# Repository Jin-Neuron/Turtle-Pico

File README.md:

<div align="right">
  <a href="README_en.md">English</a> | <b>日本語</b>
</div>

# Turtle Pico - 配線いらずで、本格的な電子工作を -

こんにちは！皆さんは、**電子工作でのお困りごと**を、どのように解決しますか？

煩雑な配線、難しいプログラミングと困難な環境構築、毎回確認が面倒なピン配置...などなど、電子工作を楽しんでいると、いくつもの壁に突き当たります。

そんな課題を克服できるようにと開発したのが、このTurtle Pico マイコンボード。ブレッドボードすら不要で、**コネクタに直接部品を接続するだけ**で回路が完成します。内部には**Raspberry Pi Pico W**を搭載しているので、プログラミングには**MicroPython**を使用でき、更にリソースにも困りません！

コネクタに超音波センサを指すと、その容姿はまるで亀のようで、その容姿から「**Turtle Pico**」とボードを名付けました。

ボードの詳細仕様は、 [Turtle Pico 仕様書](https://jinproduction.work/wp-content/uploads/2024/07/specific_ja.pdf)をご覧ください！

**本PJは現在、製品化に向けて準備中です。**

## Turtle Pico 製品パッケージ

Turtle Picoは、画像のような**パッケージ**に収納されています。

中を開けるとこのようになっていて、本体と外箱の寸法は画像に記載のとおりです。黄色が外箱、ピンクが本体の寸法です。

パッケージの中に、更にTurtle Pico本体がありますが、本体は基板を**オリジナル3Dプリンタ製カバー**で覆うような形状をしています。USBやMicroSDカードなどのコネクタポートがロゴで表示されています。

それぞれの意味は、[Turtle Pico 仕様書](https://jinproduction.work/wp-content/uploads/2024/07/specific_ja.pdf) にてご確認ください。

Turtle Picoは本体カバーの色で**カラーバリエーション**が4色あり、**ピンク色、緑色、グレー、空色**となっています。

## Turtle Pico ワクワク作例ブック

製品化モデルでは、上記の作例集が付属します。ソースコードを [example](./example/)に掲載している、TurtlePico作例の数々の作り方を掲載しています。

ここでは、作例集に掲載している、いくつかの**Turtle Picoの仲間たち**をご紹介しましょう。

画像左上は4脚でよちよちと歩くロボット「**Turtle Pico Robot**」で、サーボモータの回転で歩きます。その右側にあるのはドローン「**Turtle Pico Drone**」、更にその下にはマイコンカー「**Turtle Pico Car**」があります。

これらは、上に乗せるものを変えたり、様々な制御を追加することで、**いろいろな応用**が効きそうです。ぜひ、作例集を参考に、**自分専用のアプリケーション**に仕上げてください！

画像左下には、Turtle Picoを**サウンドカード**にしてスピーカーで音楽を流している作例です。Turtle Picoに搭載されているPCM5102AというオーディオDACは、**32bit / 192kHz**にも対応しているため、ハイレゾ音源も流せるパワフルなオーディオDACとなります。

従って、TurtlePicoは、公式にある**サウンドカード**のファームウェアを使用すれば、周囲にアンプやスピーカーをつないで、**クラフトオーディオ**を楽しむことができるボードにもなります。

作例集では、これら作例の作り方を始めとし、**応用の仕方を設計からデバッグまで**、最近の「**バイブコーディング**」でかんたんに行う**製作方法**を解説しています。Turtle Picoをお買い上げいただければ、セット担っているので、ぜひお買い求めください！

<!-- 

## Case

Turtle Pico Package is available in [**board/main/Case**](https://github.com/Jin-Neuron/Turtle-Pico/tree/master/board/main/Case).

## Purchase your board

Turtle Pico boards can currently only be purchased from [PCBWay's Shared Project Page](https://www.pcbway.com/project/shareproject/Turtle_Pico_Board_c183b11f.html). Once officially released, we plan to make it available for purchase at various online stores. 

-->

## License

本公式リポジトリは、複数のライセンスにて構成されています。

[LICENSE File](License.txt)にてご確認ください。

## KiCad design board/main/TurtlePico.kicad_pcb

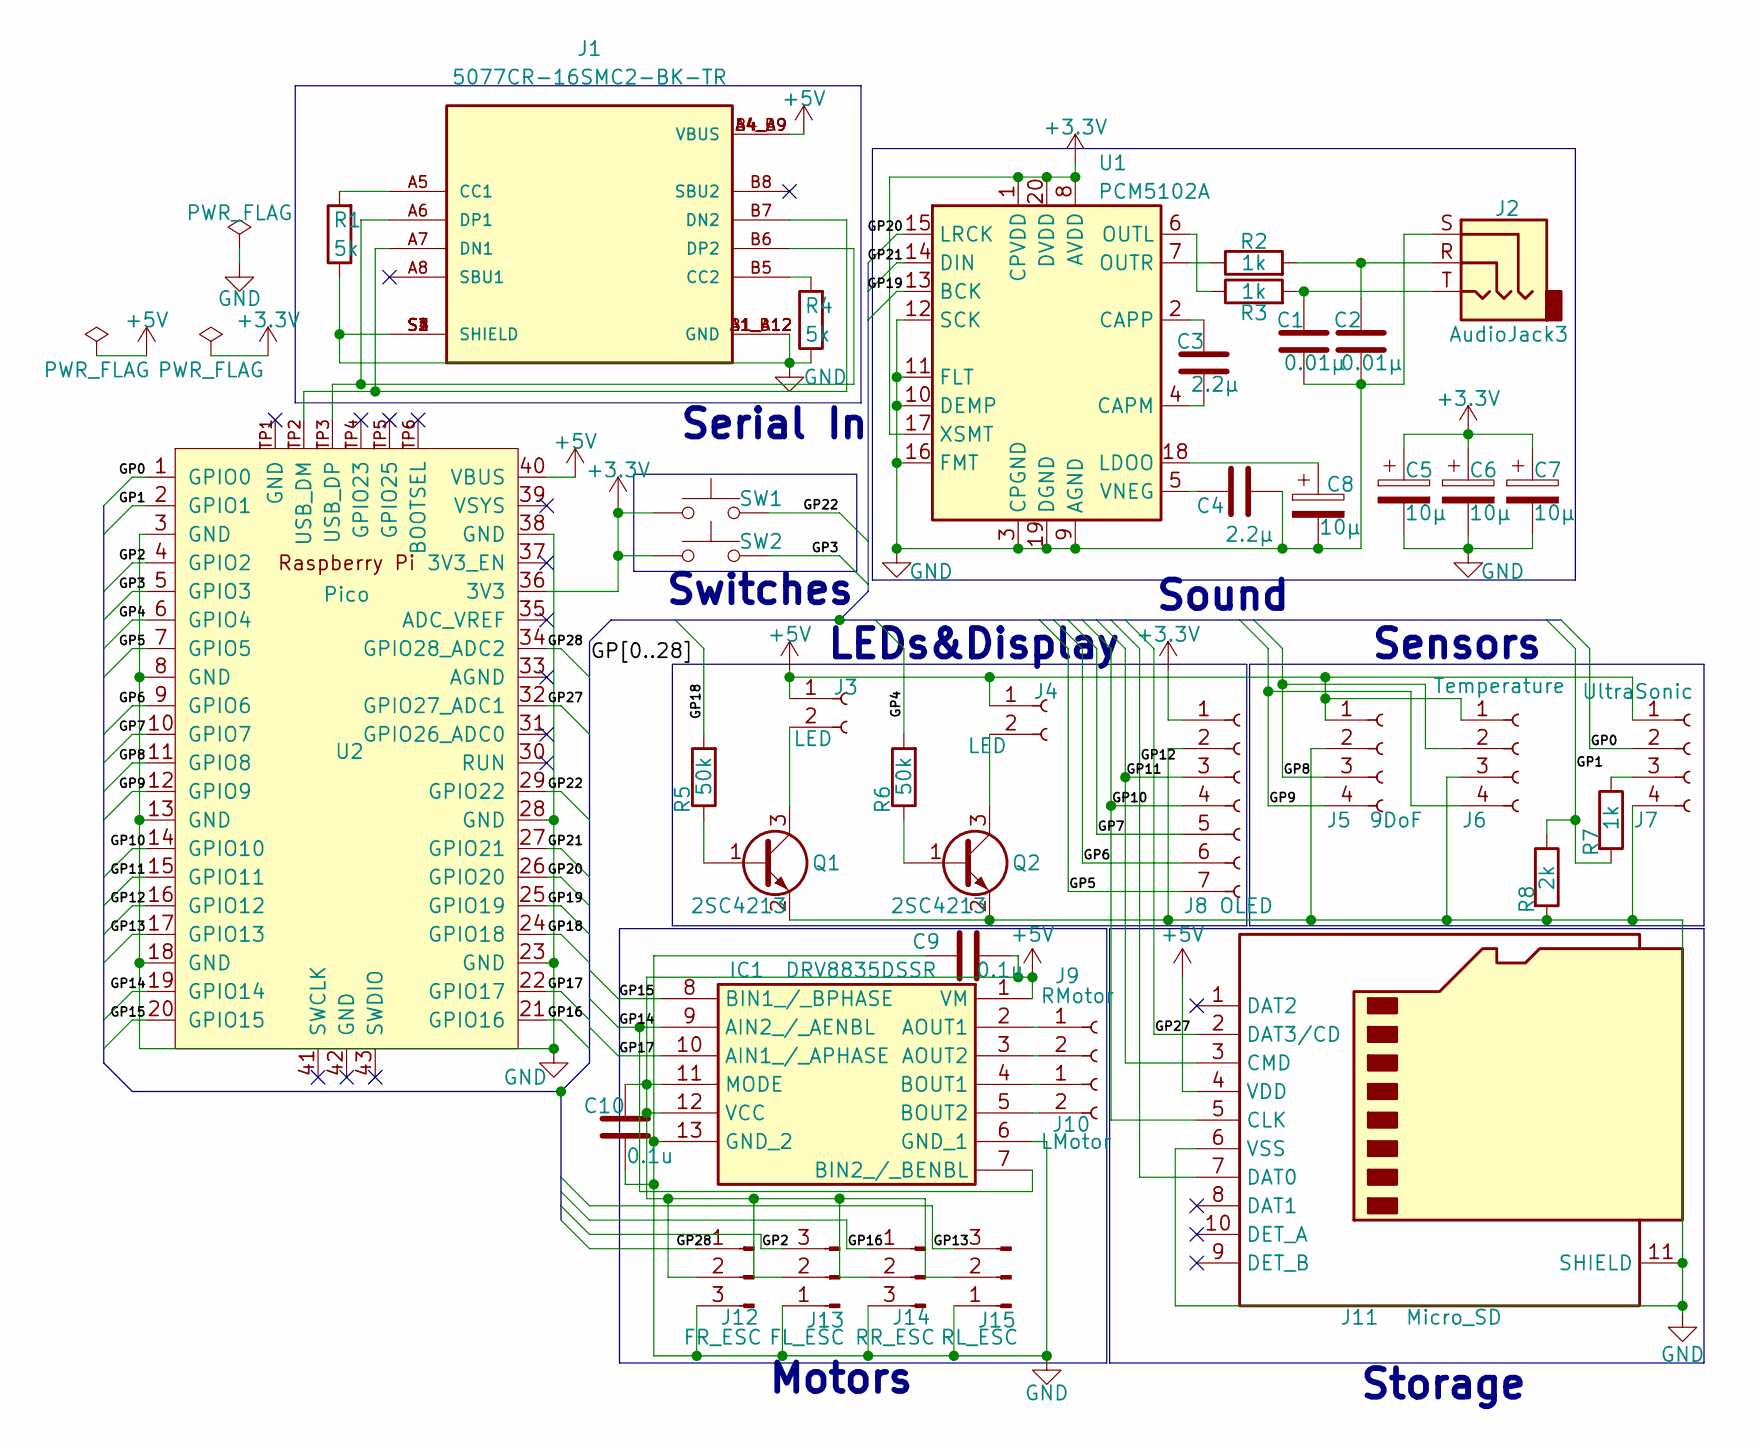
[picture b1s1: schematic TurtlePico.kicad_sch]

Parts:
C1, C2: 0.01µ; C_0603_1608Metric; Manufacturer_Part_Number GCM188R71H103KA37J; Mouser Part Number 81-GCM188R71H103KA7J
C3, C4: 2.2µ; C_0603_1608Metric; Manufacturer_Part_Number GRM188R61H225KE11D; Mouser Part Number 81-GRM188R61H225KE1D
C5, C6, C7, C8: 10µ; CP_Elec_4x5.4; Manufacturer_Part_Number EEE-FN1A100R; Mouser Part Number 667-EEE-FN1A100R
C9, C10: 0.1u; C_0603_1608Metric; Manufacturer_Part_Number GCM188R71C104KA37J; Mouser Part Number 81-GCM188R71C104KA7J
IC1: DRV8835DSSR; Mouser Part Number 595-DRV8835DSSR
J1: 5077CR-16SMC2-BK-TR; NELTRON_5077CR-16SMC2-BK-TR; Manufacturer_Part_Number USB4105-GF-A-060; Mouser Part Number 640-USB4105-GF-A-060
J2: AudioJack3; STX3000; Manufacturer_Part_Number STX-3000; Mouser Part Number 806-STX-3000
J3, J4: LED; PinSocket_1x02_P2.54mm_Vertical
J5: 9DoF; JST_XH_S4B-XH-A_1x04_P2.50mm_Horizontal
J6: Temperature; PinSocket_1x04_P2.54mm_Vertical
J7: UltraSonic; PinSocket_1x04_P2.54mm_Vertical
J8: OLED; JST_XH_S7B-XH-A_1x07_P2.50mm_Horizontal
J9: RMotor; PinSocket_1x02_P2.54mm_Vertical
J10: LMotor; PinSocket_1x02_P2.54mm_Vertical
J11: Micro_SD; microSD_HC_Hirose_DM3AT-SF-PEJM5; Manufacturer_Part_Number DM3AT-SF-PEJM5; Mouser Part Number 798-DM3AT-SF-PEJM5
J12: FR_ESC; PinHeader_1x03_P2.54mm_Horizontal
J13: FL_ESC; PinHeader_1x03_P2.54mm_Horizontal
J14: RR_ESC; PinHeader_1x03_P2.54mm_Horizontal
J15: RL_ESC; PinHeader_1x03_P2.54mm_Horizontal
Q1, Q2: 2SC4213; SOT-323_SC-70; Manufacturer_Part_Number 2SC4213-A(TE85L,F); Mouser Part Number 757-2SC4213-ATE85LF
R1, R4: 5k; R_0603_1608Metric; Manufacturer_Part_Number RN73H1JTTD5101D100; Mouser Part Number 660-RN73H1JT5101D100
R2, R3, R7: 1k; R_0603_1608Metric; Manufacturer_Part_Number RN73H1JTTD1001F100; Mouser Part Number 660-RN73H1JT1001F100
R5, R6: 50k; R_0603_1608Metric; Manufacturer_Part_Number RN73H1JTTD5102F100; Mouser Part Number 660-RN73H1JT5102F100
R8: 2k; R_0603_1608Metric; Manufacturer_Part_Number RN73H1JTTD2001F25; Mouser Part Number 660-RN73H1JTD2001F25
SW1, SW2: SW_Push; SW_SKRPACE010; Manufacturer_Part_Number SKRPACE010; Mouser Part Number 688-SKRPACE010
U1: PCM5102A; TSSOP-20_4.4x6.5mm_P0.65mm; Manufacturer_Part_Number PCM5102APWR; Mouser Part Number 595-PCM5102APWR
U2: Pico; RPi_Pico_SMD_TH; Manufacturer_Part_Number SC0918; Mouser Part Number 358-SC0918

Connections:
+3.3V: C5.1, C6.1, C7.1, J8.1, SW1.1, SW2.1, U1.1 (CPVDD), U1.8 (AVDD), U1.17 (XSMT), U1.20 (DVDD), U2.36 (3V3)
+5V: C9.1, C10.1, IC1.1 (VM), IC1.11 (MODE), IC1.12 (VCC), J1.A4_B9 (VBUS), J1.B4_A9 (VBUS), J3.1, J4.1, J5.1, J6.1, J7.1, J11.4 (VDD), J12.2, J13.2, J14.2, J15.2, U2.40 (VBUS)
/GP0: J7.2, U2.1 (GPIO0)
/GP1: R7.2, R8.1, U2.2 (GPIO1)
/GP2: J13.3, U2.4 (GPIO2)
/GP3: SW2.2, U2.5 (GPIO3)
/GP4: R6.2, U2.6 (GPIO4)
/GP5: J8.7, U2.7 (GPIO5)
/GP6: J8.6, U2.9 (GPIO6)
/GP7: J8.5, U2.10 (GPIO7)
/GP8: J5.3, J6.2, U2.11 (GPIO8)
/GP9: J5.4, J6.4, U2.12 (GPIO9)
/GP10: J8.4, J11.5 (CLK), U2.14 (GPIO10)
/GP11: J8.3, J11.3 (CMD), U2.15 (GPIO11)
/GP12: J11.7 (DAT0), U2.16 (GPIO12)
/GP13: J15.3, U2.17 (GPIO13)
/GP14: IC1.7 (BIN2_/_BENBL), IC1.9 (AIN2_/_AENBL), U2.19 (GPIO14)
/GP15: IC1.8 (BIN1_/_BPHASE), U2.20 (GPIO15)
/GP16: J14.1, U2.21 (GPIO16)
/GP17: IC1.10 (AIN1_/_APHASE), U2.22 (GPIO17)
/GP18: R5.2, U2.24 (GPIO18)
/GP19: U1.13 (BCK), U2.25 (GPIO19)
/GP20: U1.15 (LRCK), U2.26 (GPIO20)
/GP21: U1.14 (DIN), U2.27 (GPIO21)
/GP22: SW1.2, U2.29 (GPIO22)
/GP27: J11.2 (DAT3/CD), U2.32 (GPIO27_ADC1)
/GP28: J12.1, U2.34 (GPIO28_ADC2)
GND: C1.2, C2.2, C4.2, C5.2, C6.2, C7.2, C8.2, C9.2, C10.2, IC1.6 (GND_1), IC1.13 (GND_2), J1.A1_B12 (GND), J1.B1_A12 (GND), J1.S1 (SHIELD), J1.S2 (SHIELD), J1.S3 (SHIELD), J1.S4 (SHIELD), J2.S, J5.2, J6.3, J7.4, J8.2, J11.6 (VSS), J11.11 (SHIELD), J12.3, J13.1, J14.3, J15.1, Q1.2 (E), Q2.2 (E), R1.1, R4.1, R8.2, U1.3 (CPGND), U1.9 (AGND), U1.10 (DEMP), U1.11 (FLT), U1.12 (SCK), U1.16 (FMT), U1.19 (DGND), U2.3 (GND), U2.8 (GND), U2.13 (GND), U2.18 (GND), U2.23 (GND), U2.28 (GND), U2.38 (GND)
unnamed: C1.1, J2.T, R3.2
unnamed: C2.1, J2.R, R2.2
unnamed: IC1.2 (AOUT1), J9.1
unnamed: IC1.3 (AOUT2), J9.2
unnamed: IC1.4 (BOUT1), J10.1
unnamed: IC1.5 (BOUT2), J10.2
unnamed: J1.A5 (CC1), R1.2
unnamed: J1.B5 (CC2), R4.2
unnamed: J1.A7 (DN1), J1.B7 (DN2), U2.TP2 (USB_DM)
unnamed: J1.A6 (DP1), J1.B6 (DP2), U2.TP3 (USB_DP)
unnamed: J3.2, Q1.3 (C)
unnamed: J4.2, Q2.3 (C)
unnamed: J7.3, R7.1
unnamed: Q1.1 (B), R5.1
unnamed: Q2.1 (B), R6.1
unnamed: C3.2, U1.4 (CAPM)
unnamed: C3.1, U1.2 (CAPP)
unnamed: C8.1, U1.18 (LDOO)
unnamed: R3.1, U1.6 (OUTL)
unnamed: R2.1, U1.7 (OUTR)
unnamed: C4.1, U1.5 (VNEG)

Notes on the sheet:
Sensors
LEDs&Display
Serial In
Switches
Motors
Sound
Storage

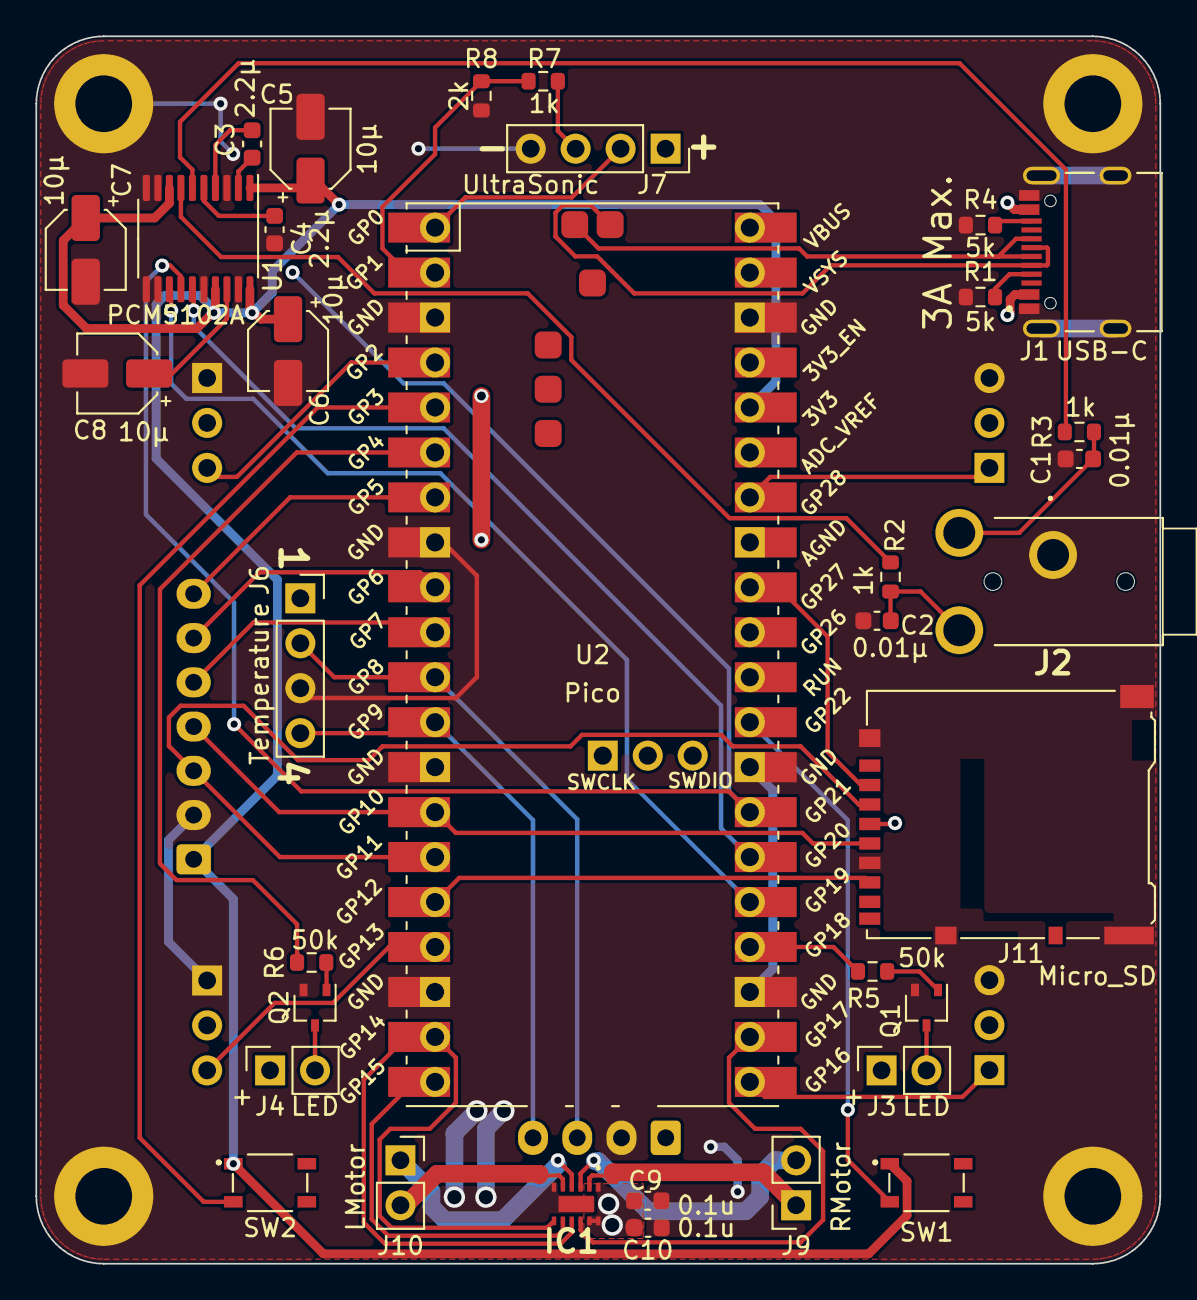
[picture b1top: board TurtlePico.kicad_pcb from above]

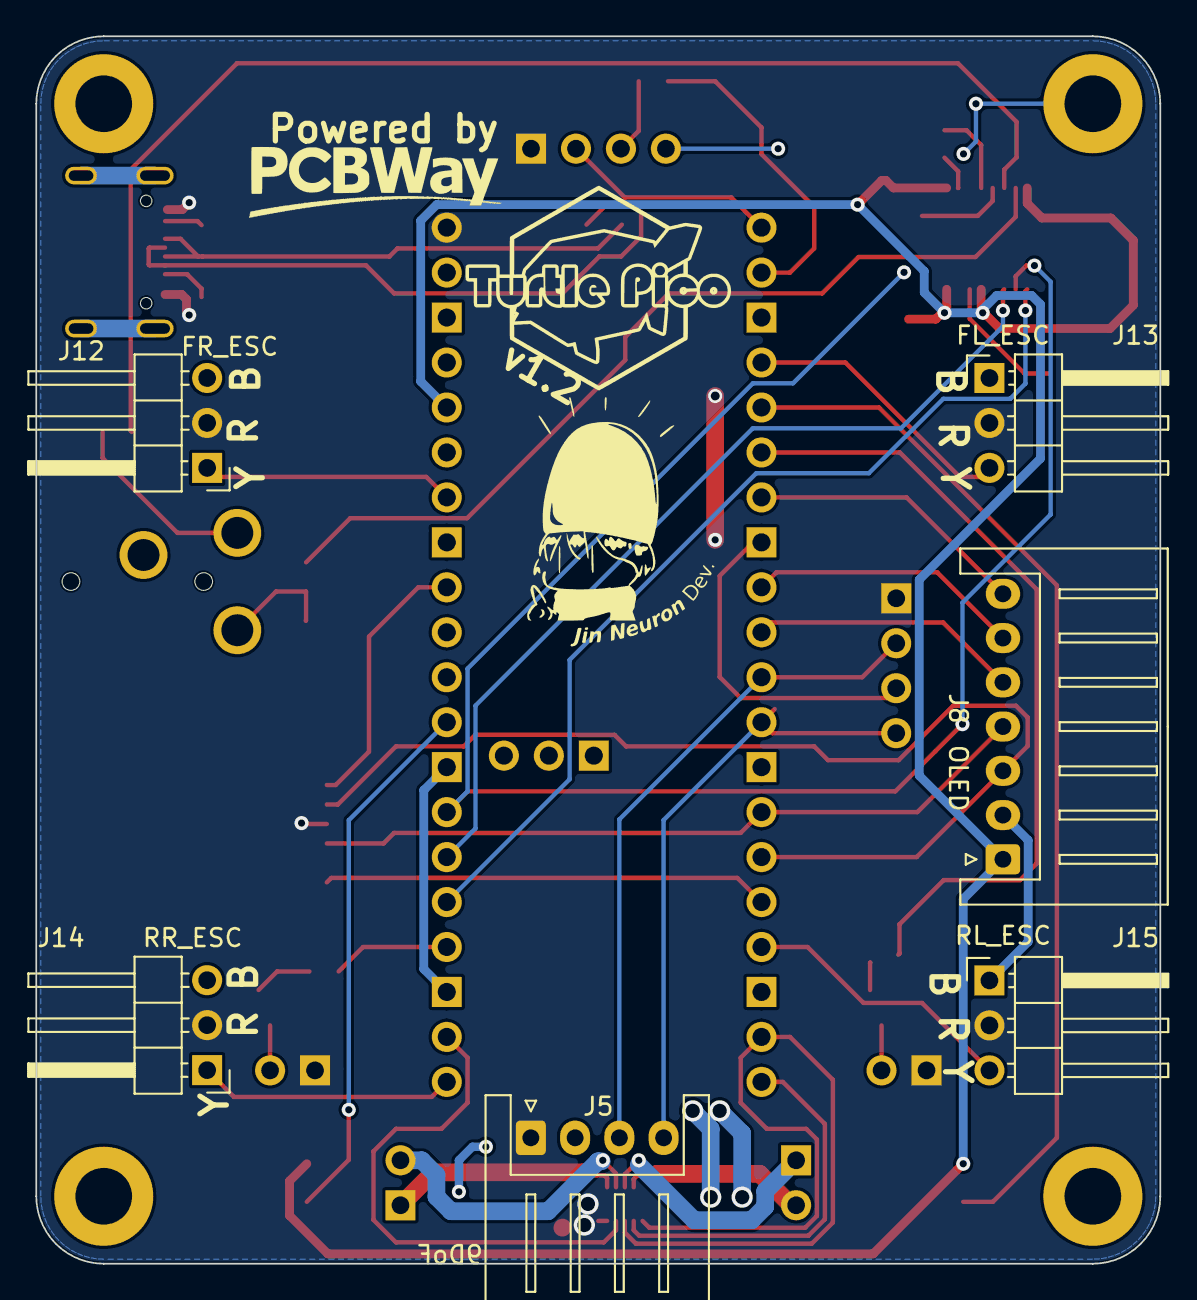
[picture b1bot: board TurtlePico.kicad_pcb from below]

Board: 2 copper layers, 63.5 x 69.3 mm, 40 parts (6 on the bottom side), 49 nets.

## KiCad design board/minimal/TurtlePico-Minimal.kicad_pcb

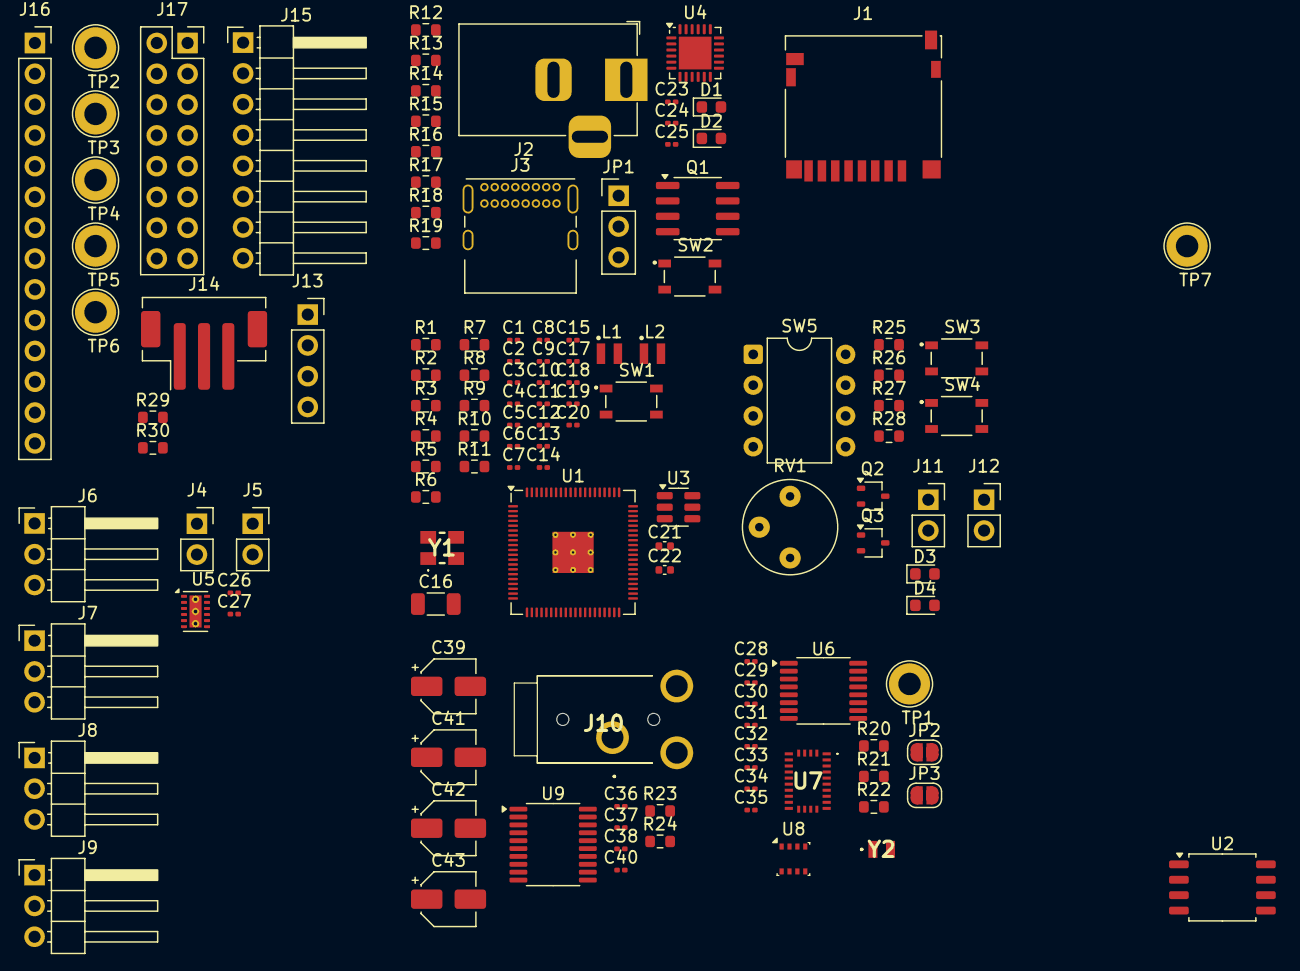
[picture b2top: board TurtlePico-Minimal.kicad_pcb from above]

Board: 2 copper layers, 126 parts (0 on the bottom side), 116 nets, no tracks yet.

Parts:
C1, C2, C4, C6: 4.7u; C_0201_0603Metric
C3, C5, C7, C8, C9, C10, C11, C12, C13, C14, C15, C17, C20, C28, C29, C32, C33: 100n; C_0201_0603Metric
C16: 10u; C_1206_3216Metric
C18, C19: 15p; C_0201_0603Metric
C21, C22: 22u; C_0402_1005Metric
C23, C24: 1u; C_0201_0603Metric
C25, C26, C27, C30, C31: 0.1u; C_0201_0603Metric
C34, C35: 20p; C_0201_0603Metric
C36, C37: 2.2µ; C_0201_0603Metric
C38, C40: 0.01µ; C_0201_0603Metric
C39, C41, C42, C43: 10µ; CP_Elec_4x5.4
D1, D2, D3, D4: LED; LED_0603_1608Metric
J1: Micro_SD; microSD_HC_Hirose_DM3D-SF
J2: Jack-DC; BarrelJack_Horizontal
J3: USB_C_Receptacle_USB2.0_16P; USB_C_Receptacle_GCT_USB4085
J4: RMotor; PinSocket_1x02_P2.54mm_Vertical
J5: LMotor; PinSocket_1x02_P2.54mm_Vertical
J6: FR_ESC; PinHeader_1x03_P2.54mm_Horizontal
J7: FL_ESC; PinHeader_1x03_P2.54mm_Horizontal
J8: RR_ESC; PinHeader_1x03_P2.54mm_Horizontal
J9: RL_ESC; PinHeader_1x03_P2.54mm_Horizontal
J10: AudioJack3; STX3000
J11, J12: LED; PinSocket_1x02_P2.54mm_Vertical
J13: UltraSonic; PinSocket_1x04_P2.54mm_Vertical
J14: Debug; JST_PH_B3B-PH-SM4-TB_1x03-1MP_P2.00mm_Vertical
J15: Display; PinHeader_1x08_P2.54mm_Horizontal
J16: TouchDisplay; PinSocket_1x14_P2.54mm_Vertical
J17: I/O Pins; PinSocket_2x08_P2.54mm_Vertical
JP1: Jumper_Power; PinHeader_1x03_P2.54mm_Vertical
JP2: Sens_SEL; SolderJumper-2_P1.3mm_Open_RoundedPad1.0x1.5mm
JP3: I2C_Addr; SolderJumper-2_P1.3mm_Open_RoundedPad1.0x1.5mm
L1: 3.3u; L_pol_2016
L2: 4.7u; L_pol_2016
Q1: DMP6050SSD; SOIC-8_3.9x4.9mm_P1.27mm
Q2, Q3: 2SC4213; SOT-323_SC-70
R1, R4, R5: 33; R_0603_1608Metric
R2, R3, R6, R7: 27; R_0603_1608Metric
R8, R9: 4.7k; R_0603_1608Metric
R10, R11, R15, R16, R17, R19, R23, R24, R25, R27, R30: 1k; R_0603_1608Metric
R12, R13, R14, R20, R21, R22: 10k; R_0603_1608Metric
R18: 100k; R_0603_1608Metric
R26, R28: 5k; R_0603_1608Metric
R29: 2k; R_0603_1608Metric
RV1: 50k; Potentiometer_Bourns_3339P_Vertical_HandSoldering
SW1: SW_Bootsel; SW_SKRPACE010
SW2: SW_Reset; SW_SKRPACE010
SW3: SW_{R}; SW_SKRPACE010
SW4: SW_{L}; SW_SKRPACE010
SW5: SW_DIP_x04; DIP-8_W7.62mm
TP1: BNO_{BOOT}; TestPoint_Loop_D2.50mm_Drill1.85mm
TP2: SPI_{MOSI}; TestPoint_Loop_D2.50mm_Drill1.85mm
TP3: SPI_{SCK}; TestPoint_Loop_D2.50mm_Drill1.85mm
TP4: SPI_{MISO}; TestPoint_Loop_D2.50mm_Drill1.85mm
TP5: I2C_{SDA}; TestPoint_Loop_D2.50mm_Drill1.85mm
TP6: I2C_{SCL}; TestPoint_Loop_D2.50mm_Drill1.85mm
TP7: GND; TestPoint_Loop_D2.50mm_Drill1.85mm
U1: RP2350B-QFN80; QFN-80-1EP_10x10mm_P0.4mm_EP3.4x3.4mm_ThermalVias
U2: W25Q128JVS; SOIC-8_5.3x5.3mm_P1.27mm
U3: AP63203WU; TSOT-23-6
U4: STUSB4500QTR; QFN-24-1EP_4x4mm_P0.5mm_EP2.7x2.7mm
U5: DRV8835DSSR; WSON-12-1EP_3x2mm_P0.5mm_EP1x2.65_ThermalVias
U6: INA260; TSSOP-16_4.4x5mm_P0.65mm
U7: BNO086
U8: BME280; Bosch_LGA-8_2.5x2.5mm_P0.65mm_ClockwisePinNumbering
U9: PCM5102A; TSSOP-20_4.4x6.5mm_P0.65mm
Y1: ABM8-272-T3; ABM8272T3
Y2: ABS06-32.768KHZ-T; ABS06

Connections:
+1V1: C2.1, C3.1, C5.1, C6.1, L1.1, U1.10 (DVDD), U1.32 (DVDD), U1.51 (DVDD), U1.65 (VREG_FB)
+2V8: C23.1, D1.2 (A), D2.2 (A), SW2.2, U4.6 (RESET), U4.23 (VREG_2V7)
+3.3V: C1.1, C7.1, C8.1, C9.1, C10.1, C11.1, C12.1, C13.1, C14.1, C15.1, C17.1, C21.1, C22.1, C26.1, C28.1, C29.1, C31.1, C32.1, C33.1, C41.1, C42.1, C43.1, J1.4 (VDD), J11.1, J12.1, J13.1, J15.1, J16.1, J17.1, L2.1, R1.1, R8.2, R9.2, R20.1, R21.1, R22.1, RV1.1, SW3.1, SW4.1, SW5.1, SW5.2, SW5.3, SW5.4, U1.5 (IOVDD), U1.15 (IOVDD), U1.24 (IOVDD), U1.29 (IOVDD), U1.41 (IOVDD), U1.50 (IOVDD), U1.59 (ADC_AVDD), U1.60 (IOVDD), U1.64 (VREG_VIN), U1.68 (USB_OTP_VDD), U1.69 (QSPI_IOVDD), U1.76 (IOVDD), U2.8 (VCC), U3.1 (FB), U5.11 (MODE), U5.12 (VCC), U6.10 (VS), U7.3 (VDD), U7.28 (VDDIO), U8.2 (CSB), U8.6 (VDDIO), U8.8 (VDD), U9.1 (CPVDD), U9.8 (AVDD), U9.17 (XSMT), U9.20 (DVDD)
CC1: J3.A5 (CC1), U4.1 (CC1DB), U4.2 (CC1)
CC2: J3.B5 (CC2), U4.4 (CC2), U4.5 (CC2DB)
D+: J3.A6 (D+), J3.B6 (D+)
D-: J3.A7 (D-), J3.B7 (D-)
Display_{BL}: J15.8, J16.8, U1.38 (GPIO30)
Display_{CS}: J15.5, J16.3, U1.4 (GPIO7)
Display_{DC}: J15.6, J16.5, U1.3 (GPIO6)
Display_{RST}: J15.7, J16.4, U1.2 (GPIO5)
ESC_{FL}: J7.3, U1.79 (GPIO2)
ESC_{FR}: J6.1, U1.36 (GPIO28)
ESC_{RL}: J9.3, U1.12 (GPIO13)
ESC_{RR}: J8.1, U1.16 (GPIO16)
Echo: R29.2, R30.1, U1.77 (GPIO0)
GND: C1.2, C2.2, C3.2, C4.2, C5.2, C6.2, C7.2, C8.2, C9.2, C10.2, C11.2, C12.2, C13.2, C14.2, C15.2, C16.2, C17.2, C18.1, C19.1, C21.2, C22.2, C23.2, C24.2, C26.2, C27.2, C28.2, C29.2, C30.1, C31.2, C32.2, C33.2, C34.1, C35.1, C37.2, C38.2, C39.2, C40.2, C41.2, C42.2, C43.2, J1.6 (VSS), J1.11 (SHIELD), J2.2, J3.A1 (GND), J3.A12 (GND), J3.B1 (GND), J3.B12 (GND), J3.S1 (SHIELD), J6.3, J7.1, J8.3, J9.1, J10.S, J13.4, J14.2, J15.2, J16.2, J17.8, J17.9, JP3.1 (A), Q2.2 (E), Q3.2 (E), R12.1, R25.1, R27.1, R29.1, RV1.3, SW1.2, TP7.1, U1.62 (VREG_PGND), U1.81 (GND), U2.4 (GND), U3.4 (GND), U4.10 (GND), U4.12 (ADDR0), U4.13 (ADDR1), U4.22 (VSYS), U4.25 (GND), U5.6 (GND_1), U5.13 (GND_2), U6.4 (A1), U6.5 (A0), U6.6 (GND), U6.11 (GND), U7.2 (GND_1), U7.5 (PS1), U7.6 (PS0/WAKE), U7.10 (CLKSEL0), U7.17 (SA0/H_MOSI), U7.25 (GND_2), U8.1 (GND), U8.7 (GND), U9.3 (CPGND), U9.9 (AGND), U9.10 (DEMP), U9.11 (FLT), U9.12 (SCK), U9.16 (FMT), U9.19 (DGND), Y1.2, Y1.4
I2S_{SCK}: U1.19 (GPIO19), U9.13 (BCK)
I2S_{SD}: U1.21 (GPIO21), U9.14 (DIN)
I2S_{WS}: U1.20 (GPIO20), U9.15 (LRCK)
I/O_{0}: J17.2, U1.43 (GPIO34)
I/O_{1}: J17.3, U1.44 (GPIO35)
I/O_{2}: J17.4, U1.45 (GPIO36)
I/O_{3}: J17.5, U1.46 (GPIO37)
I/O_{4}: J17.6, U1.47 (GPIO38)
I/O_{5}: J17.7, U1.48 (GPIO39)
I/O_{6}: J17.10, U1.52 (GPIO41_ADC1)
I/O_{7}: J17.11, U1.53 (GPIO42_ADC2)
I/O_{8}: J17.12, U1.54 (GPIO43_ADC3)
I/O_{9}: J17.13, U1.55 (GPIO44_ADC4)
I/O_{10}: J17.14, U1.56 (GPIO45_ADC5)
I/O_{11}: J17.15, U1.57 (GPIO46_ADC6)
I/O_{12}: J17.16, U1.58 (GPIO47_ADC7)
LED_{L}: D4.2 (A), R28.2, U1.1 (GPIO4)
LED_{R}: D3.2 (A), R26.2, U1.18 (GPIO18)
MOTOR_A_{EN}: U1.13 (GPIO14), U5.9 (AIN2_/_AENBL)
MOTOR_A_{IN}: U1.17 (GPIO17), U5.10 (AIN1_/_APHASE)
MOTOR_B_{EN}: U1.37 (GPIO29), U5.7 (BIN2_/_BENBL)
MOTOR_B_{IN}: U1.14 (GPIO15), U5.8 (BIN1_/_BPHASE)
unnamed: C19.2, R11.1, Y1.3
unnamed: C25.2, R19.2
unnamed: C38.1, C40.1, J10.R, J10.T, R23.2, R24.2
unnamed: D1.1 (K), R15.2
unnamed: D2.1 (K), R16.2
unnamed: D3.1 (K), R25.2
unnamed: D4.1 (K), R27.2
unnamed: J4.1, U5.2 (AOUT1)
unnamed: J4.2, U5.3 (AOUT2)
unnamed: J5.1, U5.4 (BOUT1)
unnamed: J5.2, U5.5 (BOUT2)
unnamed: J11.2, Q2.3 (C)
unnamed: J12.2, Q3.3 (C)
unnamed: J13.3, R30.2
unnamed: JP3.2 (B), R22.2, U8.5 (SDO)
unnamed: Q1.7 (D1), Q1.8 (D1), R17.2
unnamed: Q1.1 (S1), Q1.3 (S2), R18.1
unnamed: Q2.1 (B), R26.1
unnamed: Q3.1 (B), R28.1
unnamed: R10.2, SW1.1
unnamed: R12.2, SW2.1
unnamed: R4.1, U1.6 (GPIO8)
unnamed: R5.1, U1.7 (GPIO9)
unnamed: R6.2, U1.40 (GPIO32)
unnamed: R7.2, U1.42 (GPIO33)
unnamed: R3.2, U1.66 (USB_DM)
unnamed: R2.2, U1.67 (USB_DP)
unnamed: C4.1, R1.2, U1.61 (VREG_AVDD)
unnamed: L1.2, U1.63 (VREG_LX)
unnamed: C20.1, U3.6 (BST)
unnamed: C20.2, L2.2, U3.5 (SW)
unnamed: R17.1, U4.9 (DISCH)
unnamed: R15.1, U4.20 (POWER_OK2)
unnamed: R16.1, U4.14 (POWER_OK3)
unnamed: R14.1, U4.16 (VBUS_EN_SNK)
unnamed: R13.2, U4.18 (VBUS_VS_DISCH)
unnamed: C24.1, U4.21 (VREG_1V2)
unnamed: R20.2, TP1.1, U7.4 (BOOTN)
unnamed: C30.2, U7.9 (CAP)
unnamed: R21.2, U7.11 (NRST)
unnamed: C35.2, U7.27 (XIN32), Y2.1
unnamed: C34.2, U7.26 (XOUT32/CLKSEL1), Y2.2
unnamed: C36.2, U9.4 (CAPM)
unnamed: C36.1, U9.2 (CAPP)
unnamed: C39.1, U9.18 (LDOO)
unnamed: R23.1, U9.6 (OUTL)
unnamed: R24.1, U9.7 (OUTR)
unnamed: C37.1, U9.5 (VNEG)
PW_EN: Q1.2 (G1), Q1.4 (G2), R14.2, R18.2, R19.1
QSPI_{CLK}: U1.71 (QSPI_SCLK), U2.6 (CLK)
QSPI_{SD0}: U1.72 (QSPI_SD0), U2.5 (DI(IO0))
QSPI_{SD1}: U1.74 (QSPI_SD1), U2.2 (DO(IO1))
QSPI_{SD2}: U1.73 (QSPI_SD2), U2.3 (IO2)
QSPI_{SD3}: U1.70 (QSPI_SD3), U2.7 (IO3)
QSPI_{SS}: R10.1, U1.75 (QSPI_SS), U2.1 (~CS)
SCL: R5.2, R8.1, TP6.1, U4.7 (SCL), U6.9 (SCL), U7.19 (H_SCL/SCK/RX), U8.4 (SCK)
SDA: R4.2, R9.1, TP5.1, U4.8 (SDA), U6.8 (SDA), U7.20 (H_SDA/H_MISO/TX), U8.3 (SDI)
SD_{CS}: J1.2 (DAT3/CD), U1.28 (GPIO27)
SPI_{MISO}: J1.7 (DAT0), J16.9, J16.13, TP4.1, U1.11 (GPIO12)
SPI_{MOSI}: J1.3 (CMD), J15.3, J16.6, J16.12, TP2.1, U1.9 (GPIO11)
SPI_{SCK}: J1.5 (CLK), J15.4, J16.7, J16.10, TP3.1, U1.8 (GPIO10)
SWD: J14.1, U1.34 (SWDIO)
SW_{CLK}: J14.3, U1.33 (SWCLK)
SW_{DIP}1: SW5.8, U1.23 (GPIO23)
SW_{DIP}2: SW5.7, U1.25 (GPIO24)
SW_{DIP}3: SW5.6, U1.26 (GPIO25)
SW_{DIP}4: SW5.5, U1.27 (GPIO26)
SW_{L}: SW4.2, U1.80 (GPIO3)
SW_{R}: SW3.2, U1.22 (GPIO22)
TOUCH_{CS}: J16.11, U1.39 (GPIO31)
TRIG: J13.2, U1.78 (GPIO1)
VBUS: JP1.2 (C), JP2.1 (A), R13.1, U4.24 (VDD), U6.1 (IN+), U6.2 (IN+), U6.3 (IN+), U6.12 (VBUS)
VBUS_{USB}: C25.1, J3.A4 (VBUS), J3.A9 (VBUS), J3.B4 (VBUS), J3.B9 (VBUS), JP1.1 (A), JP1.3 (B), Q1.5 (D2), Q1.6 (D2)
VCC: C16.1, C27.1, J6.2, J7.2, J8.2, J9.2, JP2.2 (B), U3.2 (EN), U3.3 (IN), U5.1 (VM), U6.14 (IN-), U6.15 (IN-), U6.16 (IN-)
Volume: RV1.2, U1.49 (GPIO40_ADC0)
XIN: C18.2, U1.30 (XIN), Y1.1
XOUT: R11.2, U1.31 (XOUT)

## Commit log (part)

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2024-11-26 edit schematics
2025-04-07 bugfix I2S soundplay finished...
2025-05-04 change core to rp2350b and some pin out
2025-05-05 add some connectors
2025-05-05 change imu to BNO086
2025-05-05 set footprint
2025-05-05 add testpoint for gnd and pic of schematics
2025-05-05 change model name of minimal to advanced and name it "Leatherback"
2025-05-05 change kicad project name "Leatherback"
2025-05-08 put footprints and change schematics
2025-05-11 change schematics and complete wiring
2025-05-12 add pic
2025-05-12 add gerber
2025-05-12 remove unnecessary file
2025-08-22 some adjust PCB
2025-08-22 add nonWifi model
2026-02-20 add LTB example and more
2026-02-20 replace xh to qi
2026-02-22 update TurtlePico case
2026-02-22 add board and st7789 lib
2026-02-23 add compiled uf2 file
2026-02-23 add Leatherback board firmware
2026-02-23 add Leatherback Firmware
2026-02-23 add 2W model
2026-02-23 adjust ignore file
2026-02-23 apply 9axis example to TurtlePico Firmware
2026-02-23 apply motor and car example to TurtlePico Firmware
2026-02-23 apply led example to TurtlePico Firmware
2026-02-23 apply led_web example to TurtlePico Firmware and remove ftes
2026-02-23 apply i2s example to TurtlePico
2026-02-23 apply neopixel and motors example to TurtlePico
2026-02-23 apply musicplayer example to TurtlePico
2026-02-23 apply lcd example to TurtlePico
2026-02-23 add st7789 example
2026-02-23 update car example
2026-02-23 apply sd example to TurtlePico
2026-02-23 apply sensors_web example to TurtlePico Firmware
2026-02-23 change dir name
2026-02-23 apply servo example to TurtlePico Firmware
2026-02-23 apply temperature and smarthome example to TurtlePico Firmware
2026-02-23 apply leatherback test example to TurtlePico Firmware
2026-02-23 apply dashboard example to TurtlePico Firmware
2026-02-23 apply ultrasonic example to TurtlePico Firmware
2026-02-25 add .history
2026-02-25 edit .gitmodules
2026-02-26 add menu screen
2026-02-26 add wifi connect and loading animation
2026-02-26 add startScreen and update loading animation
2026-02-26 implement clock feature
